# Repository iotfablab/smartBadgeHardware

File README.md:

# smartBadgeHardware
This repository holds the hardware design files for the iotfablab Smart Badge.

The hardware layout has been adapted from the "Sparkfun ESP-32-Thing Plus" (https://www.sparkfun.com/products/14689) and the "Waveshare e-Paper ESP32 Driver Board" (https://www.waveshare.com/e-paper-esp32-driver-board.htm).

It is designed to work with 
* the Waveshare 2.9 inch raw e-Paper Display (https://www.waveshare.com/2.9inch-e-Paper.htm) and 
* a 1 cell 3.7V LiPo battery with 2mm JST plug (e.g. https://www.exp-tech.de/zubehoer/batterien-akkus/lipo-akkus/9365/lipo-akku-750mah-3.7-v-2-mm-jst?c=1191).

# License
<br />This work is licensed under a <a rel="license" href="http://creativecommons.org/licenses/by-sa/4.0/">Creative Commons Attribution-ShareAlike 4.0 International License</a>.

# Contact
This project has been developed as an internal project of the IoT-Fablab (www.iotfablab.eu) at BIBA - Bremer Institut für Produktion und Logistik GmbH at the University of Bremen.

For more information on the project or our lab, please feel free to contact us via info@iotfablab.eu

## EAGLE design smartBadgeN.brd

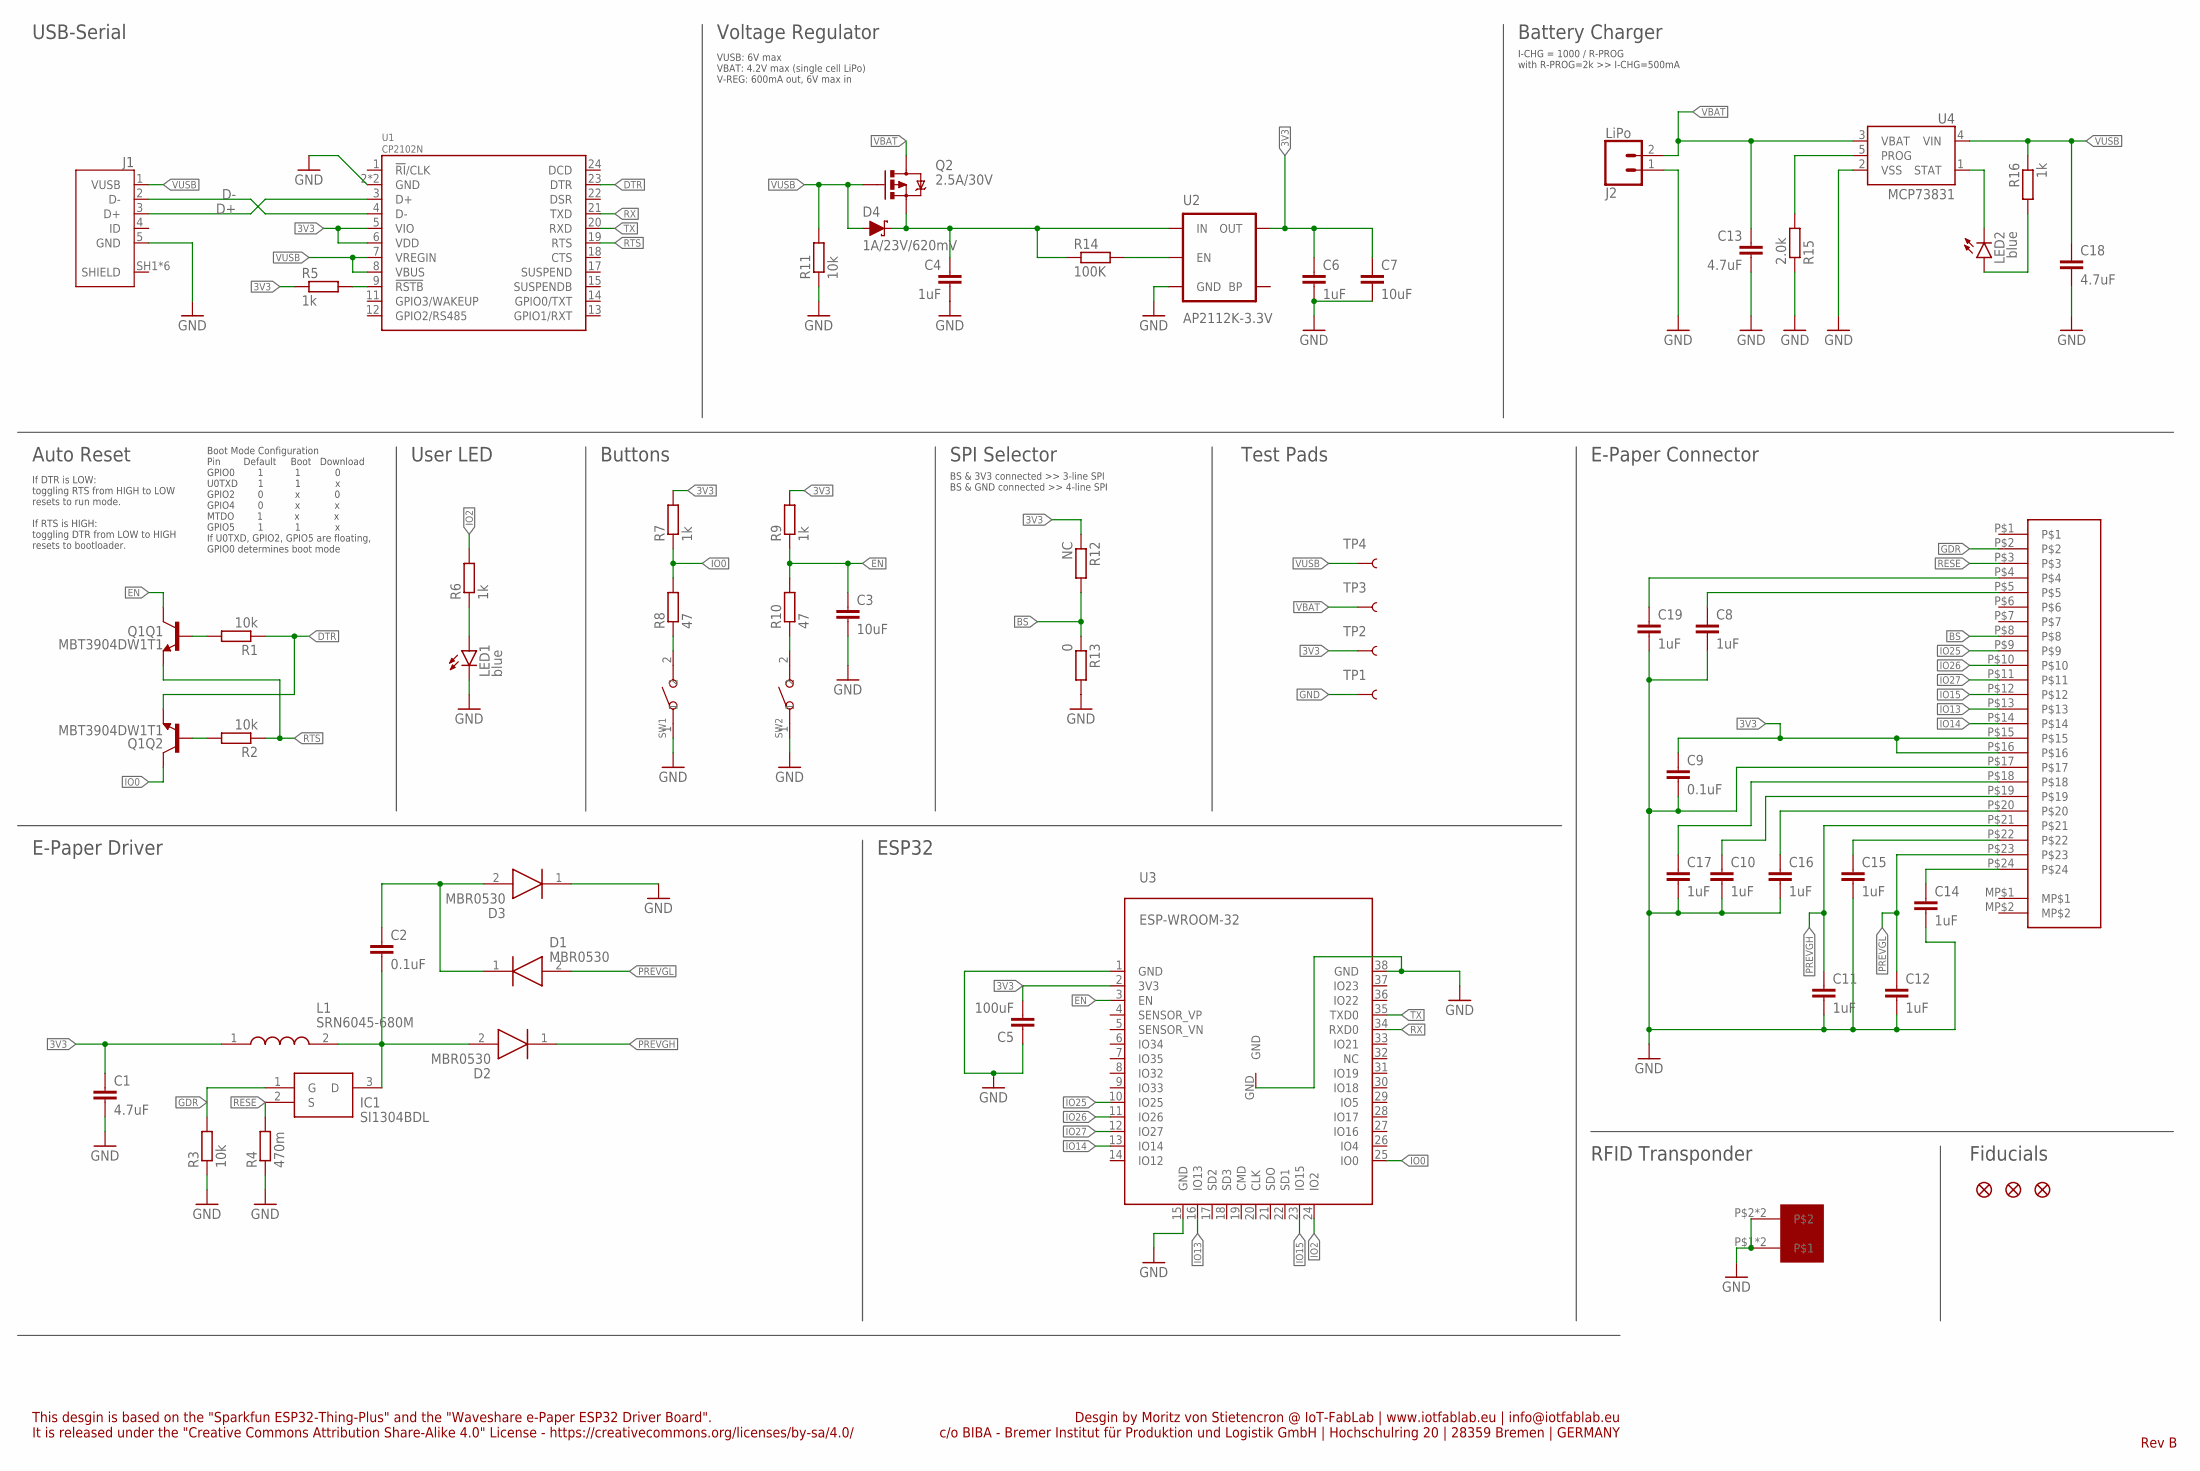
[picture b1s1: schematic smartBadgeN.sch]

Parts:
C1, C13, C18: 4.7uF; C0603
C2, C9: 0.1uF; C0603
C3, C7: 10uF; C0603
C4, C6, C8, C10, C11, C12, C14, C15, C16, C17, C19: 1uF; C0603
C5: 100uF; C1206
D1, D2, D3: MBR0530; SOD3716X135N
D4: 1A/23V/620mV; SOD-323
EPD: MOLEX-FPC-CONN-24X0.5; MOLEX-0512812494
FD1, FD2, FD3: FIDUCIAL1X2; FIDUCIAL-1X2
IC1: SI1304BDL; SOT65P210X110-3N
J1: 10118192-0001LF; AMPHENOL_10118192-0001LF
J2: LiPo; JST-2-SMD
L1: SRN6045-680M; INDPM6060X470N
LED1, LED2: blue; CHIP-LED0603
Q1: MBT3904DW1T1; SC70-6
Q2: 2.5A/30V; SOT23-3@1
R1, R2, R3, R11: 10k; R0603
R4: 470m; R0603
R5, R6, R7, R9, R16: 1k; R0603
R8, R10: 47; R0603
R12: NC; R0603
R13: 0; R0603
R14: 100K; R0603
R15: 2.0k; R0603
RFID1: LXMS21ACMF-183
SW1, SW2: SMD-BUTTON(2P-3.0X2.5X1.2+0.4MM)-B3U-1000P-2P-SMD; SW2-2.6-3.0X2.5X1.2+0.4MM
TP1, TP2, TP3, TP4: TEST-POINT3; PAD.03X.03
U1: CP2102N; QFN24
U2: AP2112K-3.3V; SOT23-5
U3: ESP-WROOM-32
U4: MCP73831; SOT23-5

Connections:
3V3: C1.1, C5.2, C6.1, C7.1, C9.1, EPD.P$15, EPD.P$16, L1.1, R5.1, R7.2, R9.2, R12.1, TP2.P$1, U1.5 (VIO), U1.6 (VDD), U2.5 (OUT), U3.2 (3V3)
BS: EPD.P$8, R12.2, R13.1
BTN1: R10.1, SW2.2
CHG: LED2.C, U4.1 (STAT)
D+: J1.3 (D+), U1.3 (D+)
D-: J1.2 (D-), U1.4 (D-)
DTR: Q1.1 (E), R1.1, U1.23 (DTR)
EN: C3.1, Q1.3 (C), R9.1, R10.2, U3.3 (EN)
EN1: R14.2, U2.3 (EN)
GDR: EPD.P$2, IC1.1 (G), R3.2
GND: C1.2, C3.2, C4.2, C5.1, C6.2, C7.2, C8.2, C9.2, C10.2, C11.2, C12.2, C13.2, C14.2, C15.2, C16.2, C17.2, C18.2, C19.2, D3.1 (K), EPD.P$17, J1.5 (GND), J2.1 (2), LED1.C, R3.1, R4.1, R11.1, R13.2, R15.1, RFID1.P$1, RFID1.P$2, RFID1.P$3, RFID1.P$4, SW1.1, SW2.1, TP1.P$1, U1.2 (GND), U1.PAD (GND), U2.2 (GND), U3.1 (GND), U3.15 (GND), U3.38 (GND), U3.GND, U4.2 (VSS)
IO0: Q1.6 (C), R7.1, R8.2, U3.25 (IO0)
IO2: R6.2, U3.24 (IO2)
IO13: EPD.P$13, U3.16 (IO13)
IO14: EPD.P$14, U3.13 (IO14)
IO15: EPD.P$12, U3.23 (IO15)
IO25: EPD.P$9, U3.10 (IO25)
IO26: EPD.P$10, U3.11 (IO26)
IO27: EPD.P$11, U3.12 (IO27)
unnamed: R5.2, U1.9 (!RSTB)
unnamed: C17.1, EPD.P$18
unnamed: C10.1, EPD.P$19
unnamed: LED2.A, R16.2
unnamed: R15.2, U4.5 (PROG)
unnamed: Q1.5 (B), R1.2
unnamed: LED1.A, R6.1
unnamed: C19.1, EPD.P$4
unnamed: C8.1, EPD.P$5
unnamed: C16.1, EPD.P$20
unnamed: C15.1, EPD.P$22
unnamed: C14.1, EPD.P$24
unnamed: C2.1, D1.1 (K), D3.2 (A)
unnamed: C2.2, D2.2 (A), IC1.3 (D), L1.2
unnamed: R8.1, SW1.2
unnamed: Q1.2 (B), R2.2
PREVGH: C11.1, D2.1 (K), EPD.P$21
PREVGL: C12.1, D1.2 (A), EPD.P$23
RESE: EPD.P$3, IC1.2 (S), R4.2
RTS: Q1.4 (E), R2.1, U1.19 (RTS)
RX: U1.21 (TXD), U3.34 (RXD0)
TX: U1.20 (RXD), U3.35 (TXD0)
VBAT: C13.1, J2.2 (1), Q2.3 (D), TP3.P$1, U4.3 (VBAT)
VIN: C4.1, D4.C, Q2.2 (S), R14.1, U2.1 (IN)
VUSB: C18.1, D4.A, J1.1 (VUSB), Q2.1 (G), R11.2, R16.1, TP4.P$1, U1.7 (VREGIN), U1.8 (VBUS), U4.4 (VIN)

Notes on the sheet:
USB-Serial
Voltage Regulator
Battery Charger
Auto Reset
User LED
E-Paper Connector
E-Paper Driver
SPI Selector
RFID Transponder
ESP32
Buttons
BS & 3V3 connected >> 3-line SPI BS & GND connected >> 4-line SPI
Fiducials
This desgin is based on the "Sparkfun ESP32-Thing-Plus" and the "Waveshare e-Paper ESP32 Driver Board". It is released under the "Creative Commons Attribution Share-Alike 4.0" License - https://creativecommons.org/licenses/by-sa/4.0/
Desgin by Moritz von Stietencron @ IoT-FabLab | www.iotfablab.eu | info@iotfablab.eu c/o BIBA - Bremer Institut für Produktion und Logistik GmbH | Hochschulring 20 | 28359 Bremen | GERMANY
Rev B
Test Pads
I-CHG = 1000 / R-PROG with R-PROG=2k >> I-CHG=500mA
VUSB: 6V max VBAT: 4.2V max (single cell LiPo) V-REG: 600mA out, 6V max in
If DTR is LOW: toggling RTS from HIGH to LOW resets to run mode. If RTS is HIGH: toggling DTR from LOW to HIGH resets to bootloader.
Boot Mode Configuration Pin Default Boot Download GPIO0 1 1 0 U0TXD 1 1 x GPIO2 0 x 0 GPIO4 0 x x MTDO 1 x x GPIO5 1 1 x If U0TXD, GPIO2, GPIO5 are floating, GPIO0 determines boot mode

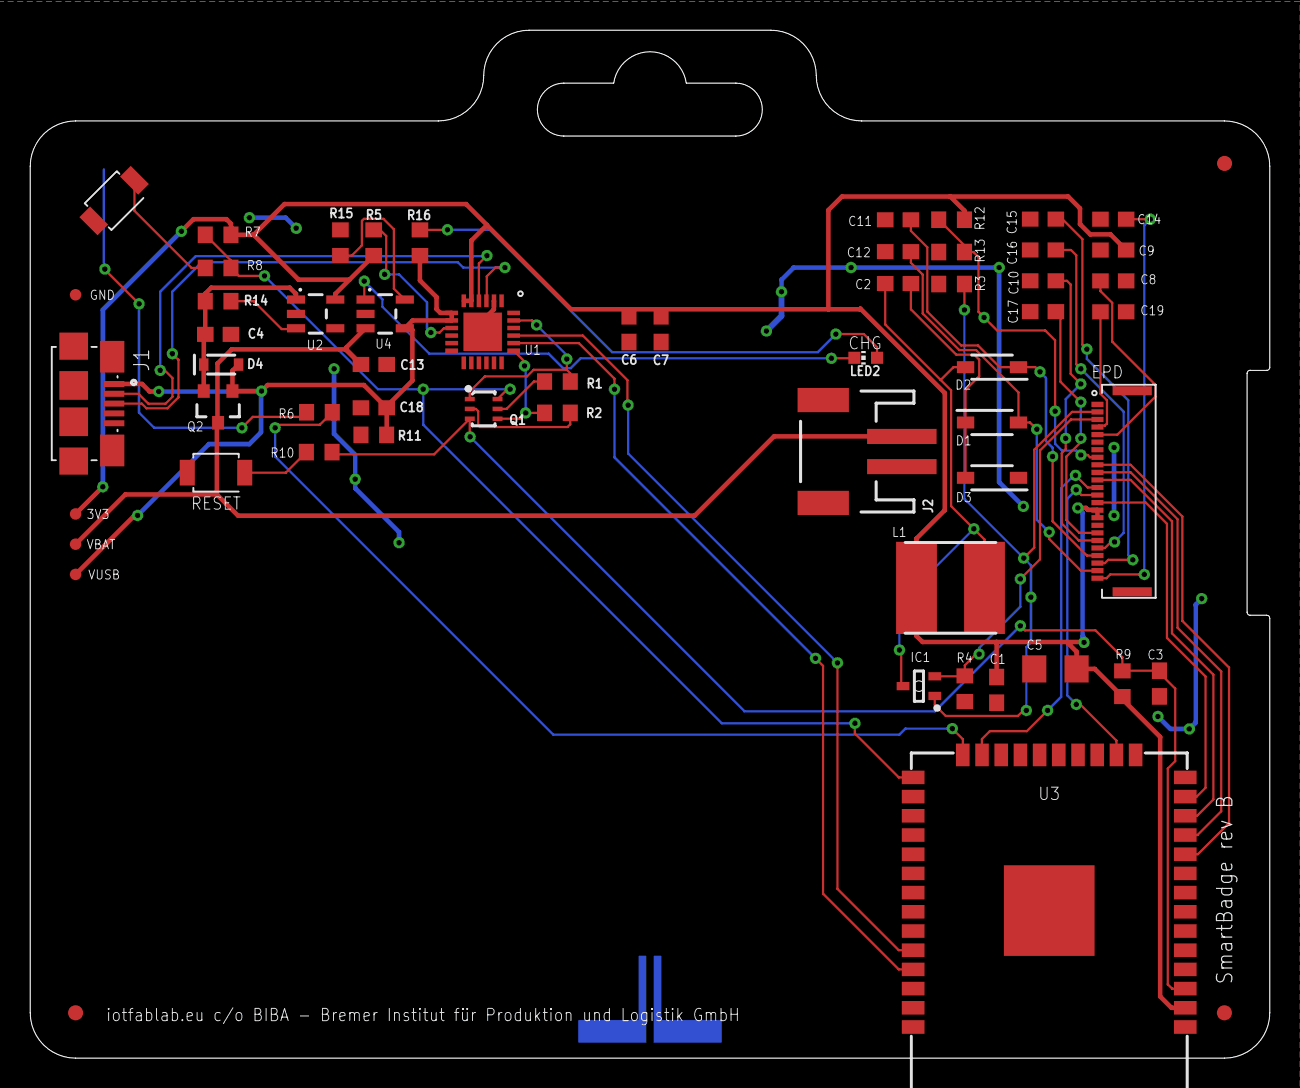
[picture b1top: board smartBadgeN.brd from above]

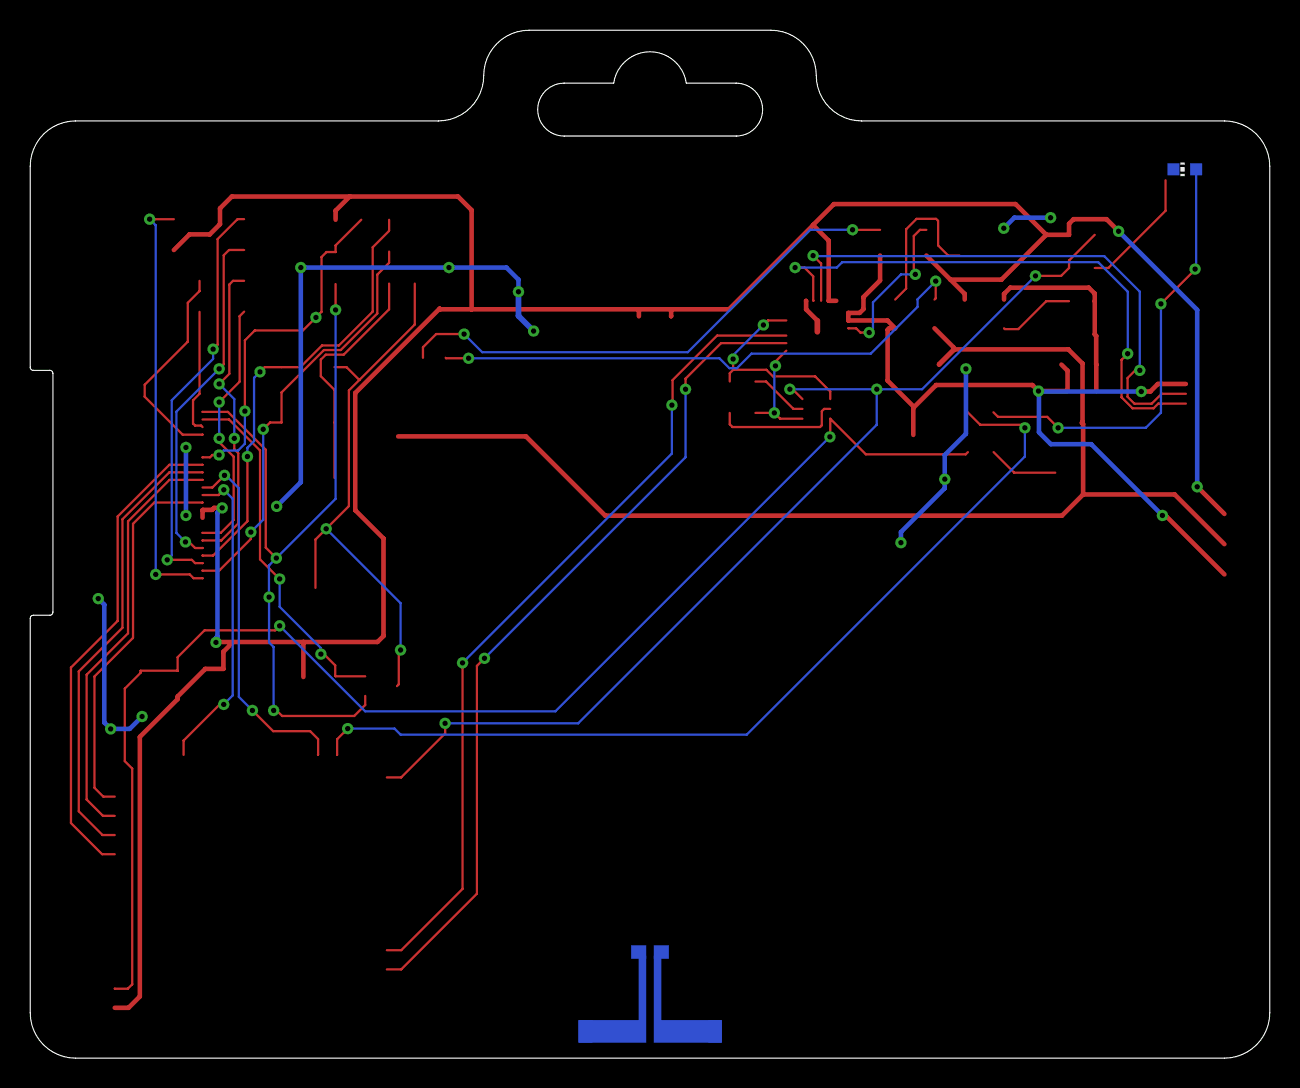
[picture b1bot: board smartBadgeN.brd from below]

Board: 2 copper layers, 82.0 x 68.0 mm, 62 parts (2 on the bottom side), 44 nets.

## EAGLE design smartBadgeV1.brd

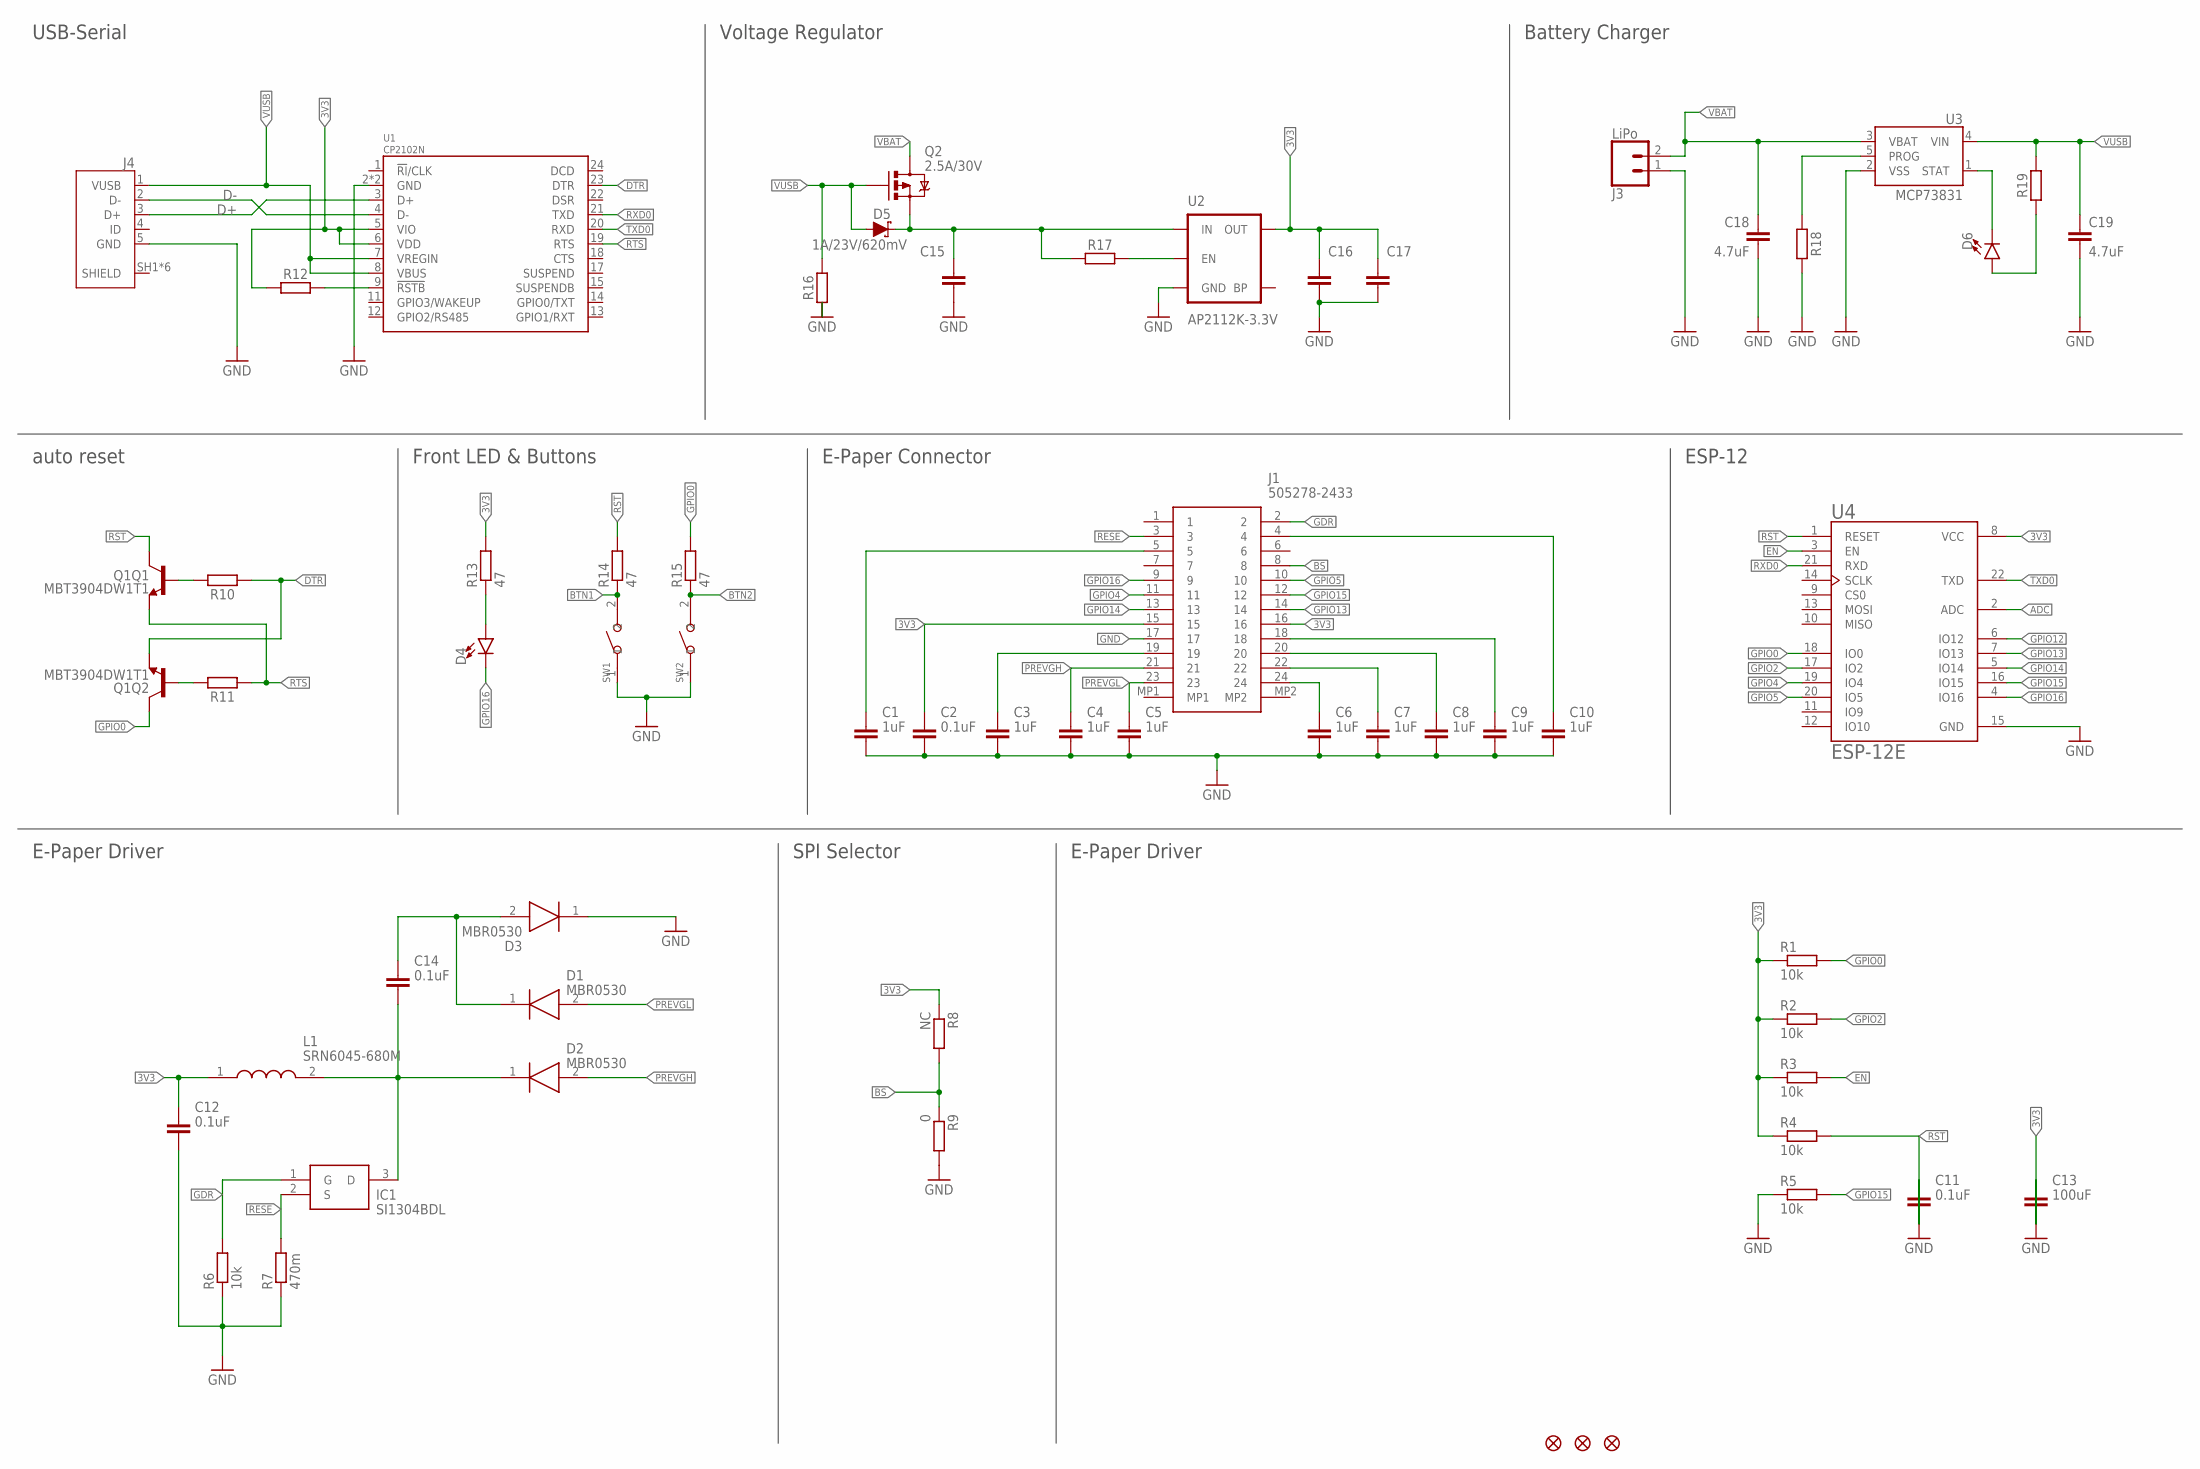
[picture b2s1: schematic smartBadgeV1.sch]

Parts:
C1, C3, C4, C5, C6, C7, C8, C9, C10, C15, C16: 1uF; C0603
C2, C11, C12, C14: 0.1uF; C0603
C13: 100uF; C1206
C17: 10uF; C0603
C18, C19: 4.7uF; 0603
D1, D2, D3: MBR0530; SOD3716X135N
D4, D6: led-blue-0603; CHIP-LED0603
D5: 1A/23V/620mV; SOD-323
FD1, FD2, FD3: FIDUCIAL1X2; FIDUCIAL-1X2
IC1: SI1304BDL; SOT65P210X110-3N
J1: 505278-2433; 5052782433
J3: LiPo; JST-2-SMD
J4: 10118192-0001LF; AMPHENOL_10118192-0001LF
L1: SRN6045-680M; INDPM6060X470N
Q1: MBT3904DW1T1; SC70-6
Q2: 2.5A/30V; SOT23-3@1
R1, R2, R3, R4, R5, R6, R10, R11, R16: 10k; R0603
R7: 470m; R0603
R8: NC; R0603
R9: 0; R0603
R12, R19: 1k; R0603
R13, R14, R15: 47; R0603
R17: 100K; R0603
R18: 2.0k; R0603
SW1, SW2: SMD-BUTTON(2P-3.0X2.5X1.2+0.4MM)-B3U-1000P-2P-SMD; SW2-2.6-3.0X2.5X1.2+0.4MM
U1: CP2102N; QFN24
U2: AP2112K-3.3V; SOT23-5
U3: MCP73831; SOT23-5
U4: ESP-12E; XCVR_ESP8266-12E/ESP-12E

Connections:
3V3: C2.1, C12.1, C13.2, C16.1, C17.1, J1.15, J1.16, L1.1, R1.1, R2.1, R3.1, R4.1, R8.1, R12.1, R13.2, U1.5 (VIO), U1.6 (VDD), U2.5 (OUT), U4.8 (VCC)
ADC: U4.2 (ADC)
BS: J1.8, R8.2, R9.1
BTN1: R14.1, SW1.2
BTN2: R15.1, SW2.2
CHG: D6.C, U3.1 (STAT)
D+: J4.3 (D+), U1.3 (D+)
D-: J4.2 (D-), U1.4 (D-)
DTR: Q1.1 (E), R10.1, U1.23 (DTR)
EN: R3.2, U4.3 (EN)
EN1: R17.2, U2.3 (EN)
GDR: IC1.1 (G), J1.2, R6.2
GND: C1.2, C2.2, C3.2, C4.2, C5.2, C6.2, C7.2, C8.2, C9.2, C10.2, C11.1, C12.2, C13.1, C15.2, C16.2, C17.2, C18.2, C19.2, D3.1 (K), J1.17, J3.1 (2), J4.5 (GND), R5.1, R6.1, R7.1, R9.2, R16.1, R18.1, SW1.1, SW2.1, U1.2 (GND), U1.PAD (GND), U2.2 (GND), U3.2 (VSS), U4.15 (GND)
GPIO0: Q1.6 (C), R1.2, R15.2, U4.18 (IO0)
GPIO2: R2.2, U4.17 (IO2)
GPIO4: J1.11, U4.19 (IO4)
GPIO5: J1.10, U4.20 (IO5)
GPIO12: U4.6 (IO12)
GPIO13: J1.14, U4.7 (IO13)
GPIO14: J1.13, U4.5 (IO14)
GPIO15: J1.12, R5.2, U4.16 (IO15)
GPIO16: D4.C, J1.9, U4.4 (IO16)
unnamed: R12.2, U1.9 (!RSTB)
unnamed: D6.A, R19.2
unnamed: R18.2, U3.5 (PROG)
unnamed: Q1.5 (B), R10.2
unnamed: D4.A, R13.1
unnamed: C1.1, J1.5
unnamed: C10.1, J1.4
unnamed: C14.1, D1.1 (K), D3.2 (A)
unnamed: C14.2, D2.1 (K), IC1.3 (D), L1.2
unnamed: C15.1, D5.C, Q2.2 (S), R17.1, U2.1 (IN)
unnamed: Q1.2 (B), R11.2
unnamed: C9.1, J1.18
unnamed: C8.1, J1.20
unnamed: C7.1, J1.22
unnamed: C6.1, J1.24
unnamed: C3.1, J1.19
PREVGH: C4.1, D2.2 (A), J1.21
PREVGL: C5.1, D1.2 (A), J1.23
RESE: IC1.2 (S), J1.3, R7.2
RST: C11.2, Q1.3 (C), R4.2, R14.2, U4.1 (RESET)
RTS: Q1.4 (E), R11.1, U1.19 (RTS)
RXD0: U1.21 (TXD), U4.21 (RXD)
TXD0: U1.20 (RXD), U4.22 (TXD)
VBAT: C18.1, J3.2 (1), Q2.3 (D), U3.3 (VBAT)
VUSB: C19.1, D5.A, J4.1 (VUSB), Q2.1 (G), R16.2, R19.1, U1.7 (VREGIN), U1.8 (VBUS), U3.4 (VIN)

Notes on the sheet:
USB-Serial
Voltage Regulator
Battery Charger
auto reset
Front LED & Buttons
E-Paper Connector
ESP-12
E-Paper Driver
SPI Selector

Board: 2 copper layers, 60 parts (1 on the bottom side), 45 nets, no tracks yet.

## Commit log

2019-06-06 hardware v1 commit
2019-08-16 first batch
2019-08-16 Deleted smartBadgeV1.brd, smartBadgeV1.pdf, smartBadgeV1.sch files
2019-08-16 revB init
2019-08-16 capacitor values updated
2019-08-22 schematics pdf added
2019-08-22 Updated License
2019-08-22 Add LICENSE

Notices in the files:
parts and their libraries:
SparkFun-Aesthetics: Licensing: Creative Commons ShareAlike 4.0 International - https://creativecommons.org/licenses/by-sa/4.0
